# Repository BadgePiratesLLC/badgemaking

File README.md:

# #badgemaking

## Badge Making Series

[01 - PCB Artwork Slide Deck](https://docs.google.com/presentation/d/e/2PACX-1vTex_8jdX296Fc8YQWmg8HyNZYr7Ur8COA3O-I2I3Fv35v6WadJ5Qk3sU4CGsJ-95iFbpAlmJvil_CP/pub?start=false&loop=false&delayms=3000)

A recorded session of this talk is available [here](https://youtu.be/qGsyMHT9-JE?t=8068)

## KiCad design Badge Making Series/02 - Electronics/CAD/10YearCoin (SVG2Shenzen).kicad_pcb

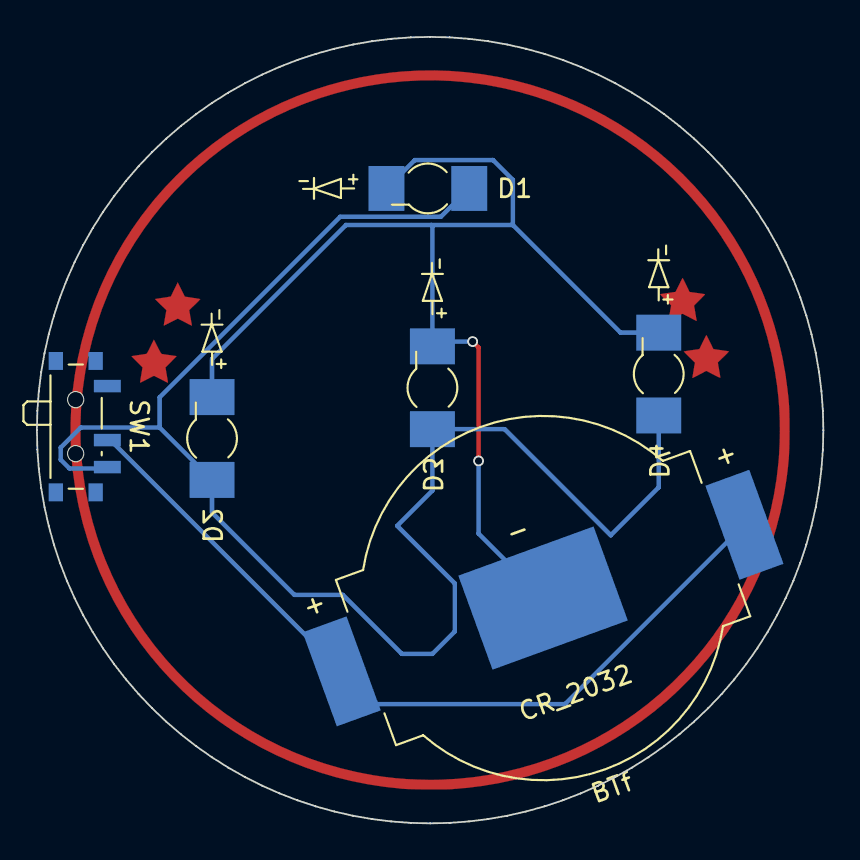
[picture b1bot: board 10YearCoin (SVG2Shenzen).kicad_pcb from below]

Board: 2 copper layers, 43.7 x 43.7 mm, 6 parts (2 on the bottom side), 3 nets.

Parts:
BTf: Battery_Cell; BatteryHolder_MPD_BC2003_1x2032
D1, D2, D3, D4: LED; LED_Osram_Lx_P47F_D2mm_ReverseMount_Proper_Mask Only
SW1: SW_SPDT; SW_SPDT_PCM12

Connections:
GND: BTf.2 (-), D1.1 (K), D2.1 (K), D3.1 (K), D4.1 (K)
unnamed: BTf.1 (+), SW1.2 (B)
unnamed: D1.2 (A), D2.2 (A), D3.2 (A), D4.2 (A), SW1.3 (C)

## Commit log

2022-01-12 Upload PCB Artwork Deck
2022-01-12 Add Demo Files for Artwork session
2022-01-12 Add image
2022-05-15 create
2022-05-15 Rename Test to Presentation and Video Coming Soon
2022-05-15 Create test
2022-05-16 Create HEre
2022-05-16 Create Videos In Order
